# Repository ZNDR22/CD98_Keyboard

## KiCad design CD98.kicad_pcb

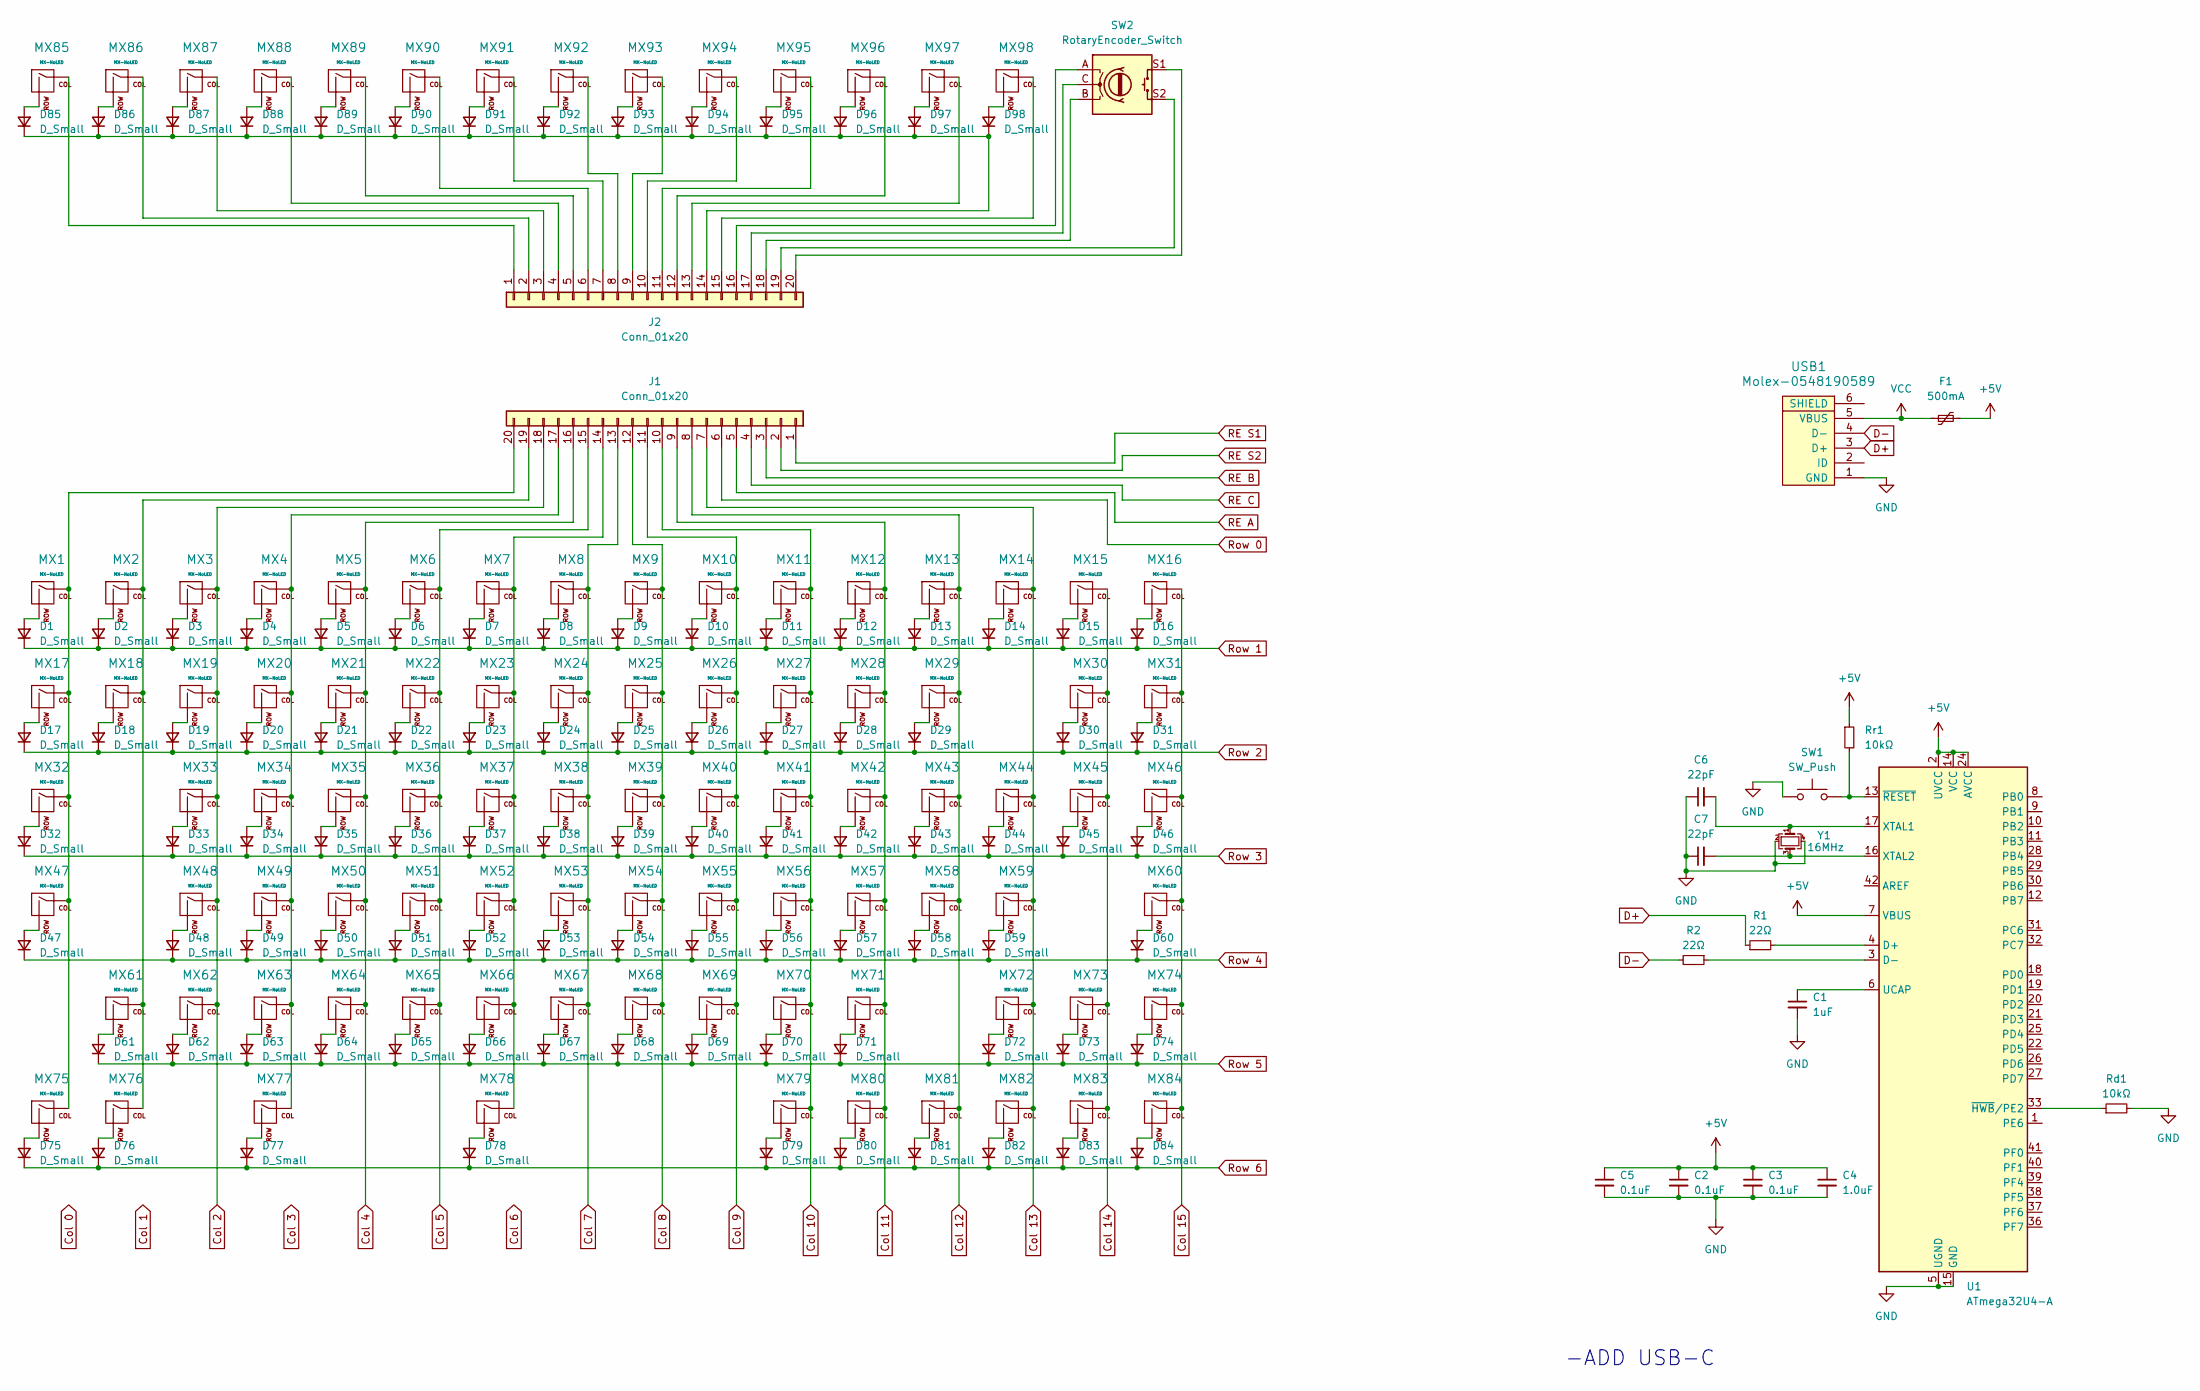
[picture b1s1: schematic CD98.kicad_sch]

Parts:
C1: 1uF; C_0805_2012Metric
C2, C3, C5: 0.1uF; C_0805_2012Metric
C4: 1.0uF; C_0805_2012Metric
C6, C7: 22pF; C_0805_2012Metric
D1, D2, D3, D4, D5, D6, D7, D8, D9, D10, D11, D12, D13, D14, D15, D16, D17, D18, D19, D20, D21, D22, D23, D24, D25, D26, D27, D28, D29, D30, D31, D32, D33, D34, D35, D36, D37, D38, D39, D40, D41, D42, D43, D44, D45, D46, D47, D48, D49, D50, D51, D52, D53, D54, D55, D56, D57, D58, D59, D60, D61, D62, D63, D64, D65, D66, D67, D68, D69, D70, D71, D72, D73, D74, D75, D76, D77, D78, D79, D80, D81, D82, D83, D84, D85, D86, D87, D88, D89, D90, D91, D92, D93, D94, D95, D96, D97, D98: D_Small; D_SOD-123
F1: 500mA; Fuse_1206_3216Metric
J1, J2: Conn_01x20; PinSocket_1x20_P2.00mm_Horizontal
MX1, MX2, MX3, MX4, MX5, MX6, MX7, MX8, MX9, MX10, MX11, MX12, MX13, MX14, MX15, MX16, MX17, MX18, MX19, MX20, MX21, MX22, MX23, MX24, MX25, MX26, MX27, MX28, MX29, MX31, MX33, MX34, MX35, MX36, MX37, MX38, MX39, MX40, MX41, MX42, MX43, MX44, MX46, MX48, MX49, MX50, MX51, MX52, MX53, MX54, MX55, MX56, MX57, MX58, MX59, MX60, MX62, MX63, MX64, MX65, MX66, MX67, MX68, MX69, MX70, MX71, MX73, MX74, MX79, MX80, MX81, MX82, MX83, MX84, MX85, MX86, MX87, MX88, MX89, MX90, MX91, MX92, MX93, MX94, MX95, MX96, MX97, MX98: MX-NoLED; MXOnly-1U-Hotswap
MX30: MX-NoLED; MXOnly-2U-Hotswap
MX32: MX-NoLED; MXOnly-1.5U-Hotswap
MX45: MX-NoLED; MXOnly-ISO-Hotswap
MX47, MX72: MX-NoLED; MXOnly-1.75U-Hotswap
MX61: MX-NoLED; MXOnly-2.25U-Hotswap
MX75, MX76, MX77: MX-NoLED; MXOnly-1.25U-Hotswap
MX78: MX-NoLED; MXOnly-6.25U-Hotswap
R1, R2: 22Ω; R_0805_2012Metric
Rd1: 10kΩ; R_0805_2012Metric
Rr1: 10kΩ; R_0805_2012Metric
SW1: SW_Push; SKQG-1155865
SW2: RotaryEncoder_Switch; RotaryEncoder_Alps_EC12E-Switch_Vertical_H20mm
U1: ATmega32U4-A; TQFP-44_10x10mm_P0.8mm
USB1: Molex-0548190589
Y1: 16MHz; Crystal_SMD_3225-4Pin_3.2x2.5mm_HandSoldering

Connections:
+5V: C2.1, C3.1, C4.1, C5.1, F1.2, Rr1.1, U1.2 (UVCC), U1.7 (VBUS), U1.14 (VCC), U1.24 (AVCC), U1.34 (VCC), U1.44 (AVCC)
Col 2: J1.18, MX3.1 (COL), MX19.1 (COL), MX33.1 (COL), MX48.1 (COL), MX62.1 (COL)
Col 4: J1.16, MX5.1 (COL), MX21.1 (COL), MX35.1 (COL), MX50.1 (COL), MX64.1 (COL)
Col 5: J1.15, MX6.1 (COL), MX22.1 (COL), MX36.1 (COL), MX51.1 (COL), MX65.1 (COL)
Col 7: J1.13, MX8.1 (COL), MX24.1 (COL), MX38.1 (COL), MX53.1 (COL), MX67.1 (COL)
Col 8: J1.12, MX9.1 (COL), MX25.1 (COL), MX39.1 (COL), MX54.1 (COL), MX68.1 (COL)
Col 9: J1.11, MX10.1 (COL), MX26.1 (COL), MX40.1 (COL), MX55.1 (COL), MX69.1 (COL)
Col 10: J1.10, MX11.1 (COL), MX27.1 (COL), MX41.1 (COL), MX56.1 (COL), MX70.1 (COL), MX79.1 (COL)
Col 11: J1.9, MX12.1 (COL), MX28.1 (COL), MX42.1 (COL), MX57.1 (COL), MX71.1 (COL), MX80.1 (COL)
Col 12: J1.8, MX13.1 (COL), MX29.1 (COL), MX43.1 (COL), MX58.1 (COL), MX81.1 (COL)
Col 13: J1.7, MX14.1 (COL), MX44.1 (COL), MX59.1 (COL), MX72.1 (COL), MX82.1 (COL)
Col 14: MX15.1 (COL), MX30.1 (COL), MX45.1 (COL), MX73.1 (COL), MX83.1 (COL)
Col 15: MX16.1 (COL), MX31.1 (COL), MX46.1 (COL), MX60.1 (COL), MX74.1 (COL), MX84.1 (COL)
D+: R1.1, USB1.3 (D+)
D-: R2.2, USB1.4 (D-)
GND: C1.2, C2.2, C3.2, C4.2, C5.2, C6.1, C7.1, Rd1.2, SW1.1, U1.5 (UGND), U1.15 (GND), U1.23 (GND), U1.35 (GND), U1.43 (GND), USB1.1 (GND), Y1.2, Y1.4
unnamed: D1.2 (A), MX1.2 (ROW)
unnamed: D2.2 (A), MX2.2 (ROW)
unnamed: D3.2 (A), MX3.2 (ROW)
unnamed: D4.2 (A), MX4.2 (ROW)
unnamed: D5.2 (A), MX5.2 (ROW)
unnamed: D6.2 (A), MX6.2 (ROW)
unnamed: D7.2 (A), MX7.2 (ROW)
unnamed: D8.2 (A), MX8.2 (ROW)
unnamed: D9.2 (A), MX9.2 (ROW)
unnamed: D10.2 (A), MX10.2 (ROW)
unnamed: D11.2 (A), MX11.2 (ROW)
unnamed: D12.2 (A), MX12.2 (ROW)
unnamed: D13.2 (A), MX13.2 (ROW)
unnamed: D14.2 (A), MX14.2 (ROW)
unnamed: D15.2 (A), MX15.2 (ROW)
unnamed: D16.2 (A), MX16.2 (ROW)
unnamed: D17.2 (A), MX17.2 (ROW)
unnamed: D18.2 (A), MX18.2 (ROW)
unnamed: D19.2 (A), MX19.2 (ROW)
unnamed: D20.2 (A), MX20.2 (ROW)
unnamed: D21.2 (A), MX21.2 (ROW)
unnamed: D22.2 (A), MX22.2 (ROW)
unnamed: D23.2 (A), MX23.2 (ROW)
unnamed: D24.2 (A), MX24.2 (ROW)
unnamed: D25.2 (A), MX25.2 (ROW)
unnamed: D26.2 (A), MX26.2 (ROW)
unnamed: D27.2 (A), MX27.2 (ROW)
unnamed: D28.2 (A), MX28.2 (ROW)
unnamed: D29.2 (A), MX29.2 (ROW)
unnamed: D30.2 (A), MX30.2 (ROW)
unnamed: D31.2 (A), MX31.2 (ROW)
unnamed: D32.2 (A), MX32.2 (ROW)
unnamed: D33.2 (A), MX33.2 (ROW)
unnamed: D34.2 (A), MX34.2 (ROW)
unnamed: D35.2 (A), MX35.2 (ROW)
unnamed: D36.2 (A), MX36.2 (ROW)
unnamed: D37.2 (A), MX37.2 (ROW)
unnamed: D38.2 (A), MX38.2 (ROW)
unnamed: D39.2 (A), MX39.2 (ROW)
unnamed: D40.2 (A), MX40.2 (ROW)
unnamed: D41.2 (A), MX41.2 (ROW)
unnamed: D42.2 (A), MX42.2 (ROW)
unnamed: D43.2 (A), MX43.2 (ROW)
unnamed: D44.2 (A), MX44.2 (ROW)
unnamed: D45.2 (A), MX45.2 (ROW)
unnamed: D46.2 (A), MX46.2 (ROW)
unnamed: D47.2 (A), MX47.2 (ROW)
unnamed: D48.2 (A), MX48.2 (ROW)
unnamed: D49.2 (A), MX49.2 (ROW)
unnamed: D50.2 (A), MX50.2 (ROW)
unnamed: D51.2 (A), MX51.2 (ROW)
unnamed: D52.2 (A), MX52.2 (ROW)
unnamed: D53.2 (A), MX53.2 (ROW)
unnamed: D54.2 (A), MX54.2 (ROW)
unnamed: D55.2 (A), MX55.2 (ROW)
unnamed: D56.2 (A), MX56.2 (ROW)
unnamed: D57.2 (A), MX57.2 (ROW)
unnamed: D58.2 (A), MX58.2 (ROW)
unnamed: D59.2 (A), MX59.2 (ROW)
unnamed: D60.2 (A), MX60.2 (ROW)
unnamed: D61.2 (A), MX61.2 (ROW)
unnamed: D62.2 (A), MX62.2 (ROW)
unnamed: D63.2 (A), MX63.2 (ROW)
unnamed: D64.2 (A), MX64.2 (ROW)
unnamed: D65.2 (A), MX65.2 (ROW)
unnamed: D66.2 (A), MX66.2 (ROW)
unnamed: D67.2 (A), MX67.2 (ROW)
unnamed: D68.2 (A), MX68.2 (ROW)
unnamed: D69.2 (A), MX69.2 (ROW)
unnamed: D70.2 (A), MX70.2 (ROW)
unnamed: D71.2 (A), MX71.2 (ROW)
unnamed: D72.2 (A), MX72.2 (ROW)
unnamed: D73.2 (A), MX73.2 (ROW)
unnamed: D74.2 (A), MX74.2 (ROW)
unnamed: D75.2 (A), MX75.2 (ROW)
unnamed: D76.2 (A), MX76.2 (ROW)
unnamed: D77.2 (A), MX77.2 (ROW)
unnamed: D78.2 (A), MX78.2 (ROW)
unnamed: D79.2 (A), MX79.2 (ROW)
unnamed: D80.2 (A), MX80.2 (ROW)
unnamed: D81.2 (A), MX81.2 (ROW)
unnamed: D82.2 (A), MX82.2 (ROW)
unnamed: D83.2 (A), MX83.2 (ROW)
unnamed: D84.2 (A), MX84.2 (ROW)
unnamed: D85.2 (A), MX85.2 (ROW)
unnamed: D85.1 (K), D86.1 (K), D87.1 (K), D88.1 (K), D89.1 (K), D90.1 (K), D91.1 (K), D92.1 (K), D93.1 (K), D94.1 (K), D95.1 (K), D96.1 (K), D97.1 (K), D98.1 (K), J2.14
unnamed: D86.2 (A), MX86.2 (ROW)
unnamed: D87.2 (A), MX87.2 (ROW)
unnamed: D88.2 (A), MX88.2 (ROW)
unnamed: D89.2 (A), MX89.2 (ROW)
unnamed: D90.2 (A), MX90.2 (ROW)
unnamed: D91.2 (A), MX91.2 (ROW)
unnamed: D92.2 (A), MX92.2 (ROW)
unnamed: D93.2 (A), MX93.2 (ROW)
unnamed: D94.2 (A), MX94.2 (ROW)
unnamed: D95.2 (A), MX95.2 (ROW)
unnamed: D96.2 (A), MX96.2 (ROW)
unnamed: D97.2 (A), MX97.2 (ROW)
unnamed: D98.2 (A), MX98.2 (ROW)
unnamed: J1.14, MX7.1 (COL), MX23.1 (COL), MX37.1 (COL), MX52.1 (COL), MX66.1 (COL), MX78.1 (COL)
unnamed: J1.17, MX4.1 (COL), MX20.1 (COL), MX34.1 (COL), MX49.1 (COL), MX63.1 (COL), MX77.1 (COL)
unnamed: J1.19, MX2.1 (COL), MX18.1 (COL), MX61.1 (COL), MX76.1 (COL)
unnamed: J1.20, MX1.1 (COL), MX17.1 (COL), MX32.1 (COL), MX47.1 (COL), MX75.1 (COL)
unnamed: J2.1, MX85.1 (COL)
unnamed: J2.2, MX86.1 (COL)
unnamed: J2.3, MX87.1 (COL)
unnamed: J2.4, MX88.1 (COL)
unnamed: J2.5, MX89.1 (COL)
unnamed: J2.6, MX90.1 (COL)
unnamed: J2.7, MX91.1 (COL)
unnamed: J2.8, MX92.1 (COL)
unnamed: J2.9, MX93.1 (COL)
unnamed: J2.10, MX94.1 (COL)
unnamed: J2.11, MX95.1 (COL)
unnamed: J2.12, MX96.1 (COL)
unnamed: J2.13, MX97.1 (COL)
unnamed: J2.15, MX98.1 (COL)
unnamed: J2.16, SW2.A
unnamed: J2.17, SW2.C
unnamed: J2.18, SW2.B
unnamed: J2.19, SW2.S2
unnamed: J2.20, SW2.S1
unnamed: R1.2, U1.4 (D+)
unnamed: R2.1, U1.3 (D-)
unnamed: C1.1, U1.6 (UCAP)
unnamed: C6.2, U1.17 (XTAL1), Y1.1
unnamed: C7.2, U1.16 (XTAL2), Y1.3
unnamed: Rd1.1, U1.33 (~HWB/PE2)
unnamed: Rr1.2, SW1.2, U1.13 (~RESET)
RE A: J1.5
RE B: J1.3
RE C: J1.4
RE S1: J1.1
RE S2: J1.2
Row 0: J1.6
Row 1: D1.1 (K), D2.1 (K), D3.1 (K), D4.1 (K), D5.1 (K), D6.1 (K), D7.1 (K), D8.1 (K), D9.1 (K), D10.1 (K), D11.1 (K), D12.1 (K), D13.1 (K), D14.1 (K), D15.1 (K), D16.1 (K)
Row 2: D17.1 (K), D18.1 (K), D19.1 (K), D20.1 (K), D21.1 (K), D22.1 (K), D23.1 (K), D24.1 (K), D25.1 (K), D26.1 (K), D27.1 (K), D28.1 (K), D29.1 (K), D30.1 (K), D31.1 (K)
Row 3: D32.1 (K), D33.1 (K), D34.1 (K), D35.1 (K), D36.1 (K), D37.1 (K), D38.1 (K), D39.1 (K), D40.1 (K), D41.1 (K), D42.1 (K), D43.1 (K), D44.1 (K), D45.1 (K), D46.1 (K)
Row 4: D47.1 (K), D48.1 (K), D49.1 (K), D50.1 (K), D51.1 (K), D52.1 (K), D53.1 (K), D54.1 (K), D55.1 (K), D56.1 (K), D57.1 (K), D58.1 (K), D59.1 (K), D60.1 (K)
Row 5: D61.1 (K), D62.1 (K), D63.1 (K), D64.1 (K), D65.1 (K), D66.1 (K), D67.1 (K), D68.1 (K), D69.1 (K), D70.1 (K), D71.1 (K), D72.1 (K), D73.1 (K), D74.1 (K)
Row 6: D75.1 (K), D76.1 (K), D77.1 (K), D78.1 (K), D79.1 (K), D80.1 (K), D81.1 (K), D82.1 (K), D83.1 (K), D84.1 (K)
VCC: F1.1, USB1.5 (VBUS)

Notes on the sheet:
-ADD USB-C

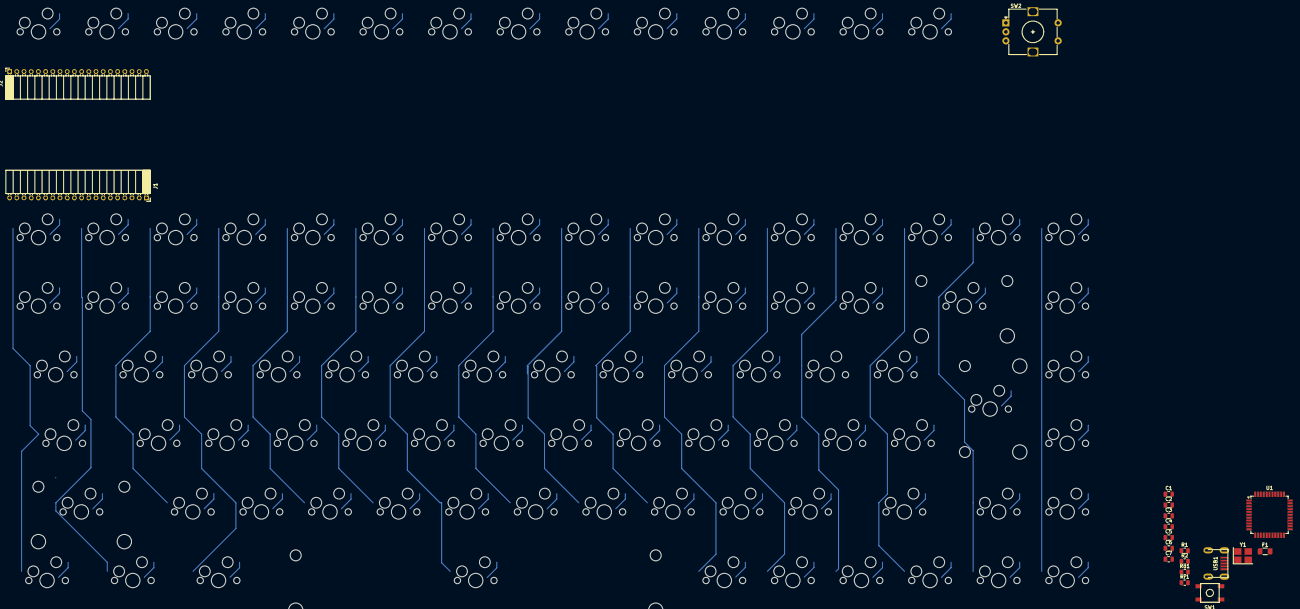
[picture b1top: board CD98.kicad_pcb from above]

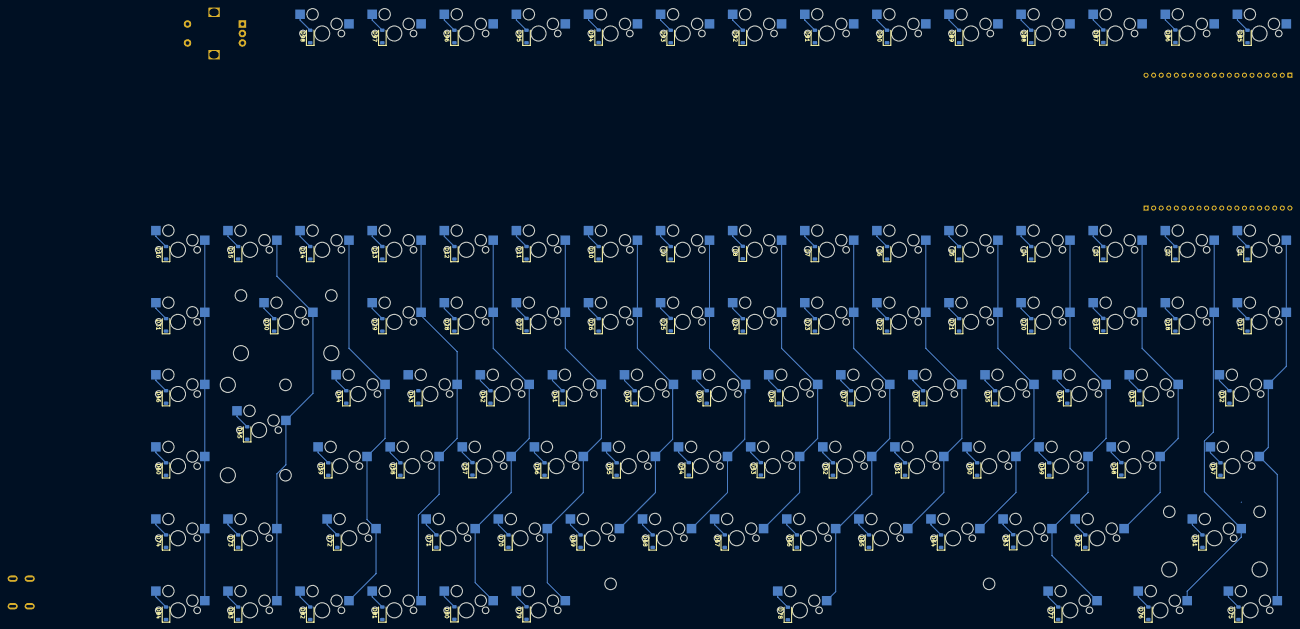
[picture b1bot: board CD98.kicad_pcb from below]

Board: 2 copper layers, 215 parts (98 on the bottom side), 152 nets.

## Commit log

2024-08-06 v5
    Basic setup, local libraries added.
2024-08-06 CD98 Keyboard v5
    Wired matrix, included secondary board.
2024-08-06 CD98 Keyboard v5
2024-08-08 v5
    Remapped error from previous schematic, positioned key switches in pcb.
2024-08-09 v5
    Repositioned diodes, wired matrix.
